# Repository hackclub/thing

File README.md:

<picture>
  <source media="(prefers-color-scheme: dark) and (max-width: 960px)" srcset="./thing.png">
  <source media="(prefers-color-scheme: dark) and (min-width: 961px)" width="50%" srcset="./thing.png">

  <source media="(prefers-color-scheme: light) and (max-width: 960px)" srcset="./thing-light.png">
  <source media="(prefers-color-scheme: light) and (min-width: 961px)" width="50%" srcset="./thing-light.png">

</picture>

Hey! Welcome to **The Thing**!

## Hey, what is this thing?
Have you seen those 80-part Swiss Army knives? I want us to make a PCB with that level of esotericism; a sprawling, over-the-top monstrosity.

Many Hack Clubbers will add a tool or something to the same PCB consecutively, and at the end I'll get \~10 made and send them off to some people you may or may not have seen on YouTube...
(and if you find me at a hackathon and you've added a subsystem to the board you may end up with one too (prob limited to 1 or 2)).

It'll end when 100 subsystems have been added or nobody adds a component for a week. Happy hacking!

## Current thing:

## How will it work?
* People will take turns adding their subsystem.
* Each person will get 2 days. If it's not merged after exactly 2 days, you'll be put at the back of the queue for another go and it'll be handed off to the next person. **I'll DM you a day or two before it's your turn to make sure you're ready. If you don't respond you might be skipped.**
* Merging requires me to be reasonably sure it'll work.

## What should my submission include?
* In the `/docs` directory, add a folder titled `IDX-USERNAME`, where `IDX` is your number in line, and `USERNAME` is your GitHub username.
  * For example, I'm the first person to go, so my folder is named `0-malted`.
  * In your folder, you'll need;
    * `doc.md`: Your writeup. Include detail about your subsystem! How you designed it, your calculations, tests, everything. Don't use an LLM, make it interesting, tell me a story!! :D
    * `pcb.png`: A screenshot of the PCB in Kicad's PCB editor, showing the entire PCB.
    * `pcb-3d.png`: Switch to View > 3D viewer and select "Render current view using raytracing". Again, we want to see the whole board!
    * `schematic.png`: A screenshot of the whole board's schematic.
    * `cad.png` **(OPTIONAL)**: If someone designs an enclosure or something (wink wink nudge nudge), show me a screenshot of it. You only need to do this if you've changed it.
    * `bom.csv`: Your bill of materials. Create and edit this manually. The price should be that of a single part (regardless of your `quantity`, **on the line item for 100 pieces**. It should be in USD without a dollar symbol.
      * For an exemplar BoM check mine out: `/docs/0-malted/bom.csv`. There's a template at `/docs/bom-template.csv`.
  * Make your schematic as complete as possible! When you double click your components you can add datasheets to help out others who might need to tie into your circuit or something in the future.

## Constraints
* Use Kicad `9.0.x`. Apparently, our project will be corrupted if we're on differing versions.
* Each BoM must not exceed $5 in parts. Assume 3D printing is free. If you have an especially cool idea I could be convinced to double it on a case-by-case basis :)
* Please strongly bias for parts in stock on Digikey.

## Tips
Finding parts can be tricky. Here's how I found the USB-C receptable I used in my circuit;
  1. Added a symbol to my schematic. I only wanted it for the 5V rail, so I found a symbol with the description "*USB Power-Only 6P Type-C Receptacle connector*". Seems okay.
  2. Opened the *footprint editor* and searched for "*usb c receptacle 6p*" (6P meaning it has 6 pins, which is minimal). I found a footprint named "*USB_C_Receptacle_GCT_USB4125-xx-x_6P_TopMnt_Horizontal*", which looked good. I liked the footprint because it had through-hole shield pins, meaning it would be less likely to be ripped off the board when pulling on it. The only other footprint which actually had 6 pins didn't have the through-hole shield.
  3. I searched on the internet for "*USB4125*". I found the [page from the manufacturer](https://gct.co/connector/usb4125) (GCT), which had links to Mouser and Digikey, amongst others. Heaven. It was slightly cheaper on Mouser so I went with that. It's comforting that it says *21230 In stock*.
  4. I double click on my component, click the library icon at the end of the "Footprint" table row, and searched for "*gct usb 4125*". Assigned it. Placed it on my PCB, and added it to my BoM! All done.

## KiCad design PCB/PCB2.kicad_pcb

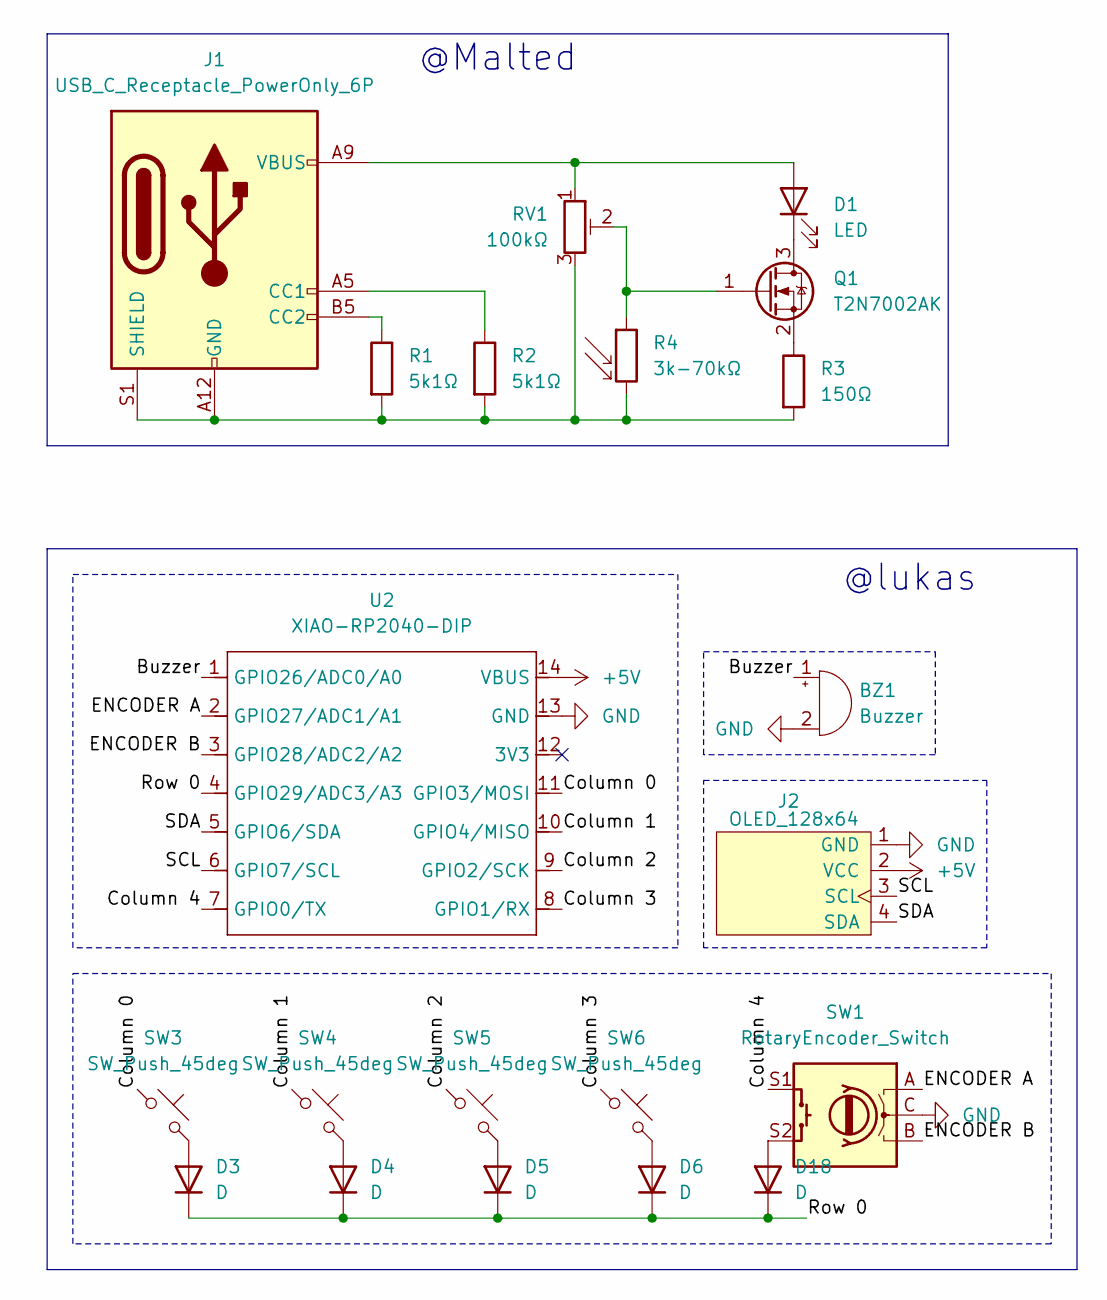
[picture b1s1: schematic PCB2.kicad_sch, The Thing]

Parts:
BZ1: Buzzer; Buzzer_12x9.5RM7.6
D1: LED; LED_D5.0mm_Clear
D3, D4, D5, D6, D18: D; Diode_SOD-123
J1: USB_C_Receptacle_PowerOnly_6P; USB_C_Receptacle_GCT_USB4125-xx-x-0190_6P_TopMnt_Horizontal
J2: OLED_128x64; OLED_128x32
Q1: T2N7002AK; SOT-23
R1, R2: 5k1Ω; R_0402_1005Metric
R3: 150Ω; R_0402_1005Metric
R4: 3k-70kΩ; R_LDR_5.1x4.3mm_P3.4mm_Vertical
RV1: 100kΩ; Potentiometer_Bourns_TC33X_Vertical
SW1: RotaryEncoder_Switch; RollerEncoder_Panasonic_EVQWGD001
SW3, SW4, SW5, SW6: SW_Push_45deg; MX-Solderable-1U
U2: XIAO-RP2040-DIP

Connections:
+5V: J2.2 (VCC), U2.14 (VBUS)
/BUZZER PASSIVE: BZ1.1 (+), U2.1 (GPIO26/ADC0/A0)
/Column 0: SW3.1, U2.11 (GPIO3/MOSI)
/Column 1: SW4.1, U2.10 (GPIO4/MISO)
/Column 2: SW5.1, U2.9 (GPIO2/SCK)
/Column 3: SW6.1, U2.8 (GPIO1/RX)
/Column 4: SW1.S1, U2.7 (GPIO0/TX)
/ENCODER A: SW1.A, U2.2 (GPIO27/ADC1/A1)
/ENCODER B: SW1.B, U2.3 (GPIO28/ADC2/A2)
/Row 0: D3.1 (K), D4.1 (K), D5.1 (K), D6.1 (K), D18.1 (K), U2.4 (GPIO29/ADC3/A3)
/SCL: J2.3 (SCL), U2.6 (GPIO7/SCL)
/SDA: J2.4 (SDA), U2.5 (GPIO6/SDA)
GND: BZ1.2 (-), J2.1 (GND), SW1.C, U2.13 (GND)
unnamed: D1.2 (A), J1.A9 (VBUS), J1.B9 (VBUS), RV1.1
unnamed: D1.1 (K), Q1.3 (D)
unnamed: D3.2 (A), SW3.2
unnamed: D4.2 (A), SW4.2
unnamed: D5.2 (A), SW5.2
unnamed: D6.2 (A), SW6.2
unnamed: D18.2 (A), SW1.S2
unnamed: J1.A5 (CC1), R2.1
unnamed: J1.B5 (CC2), R1.1
unnamed: J1.A12 (GND), J1.B12 (GND), J1.S1 (SHIELD), R1.2, R2.2, R3.2, R4.2, RV1.3
unnamed: Q1.1 (G), R4.1, RV1.2
unnamed: Q1.2 (S), R3.1

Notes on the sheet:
@Malted
@lukas

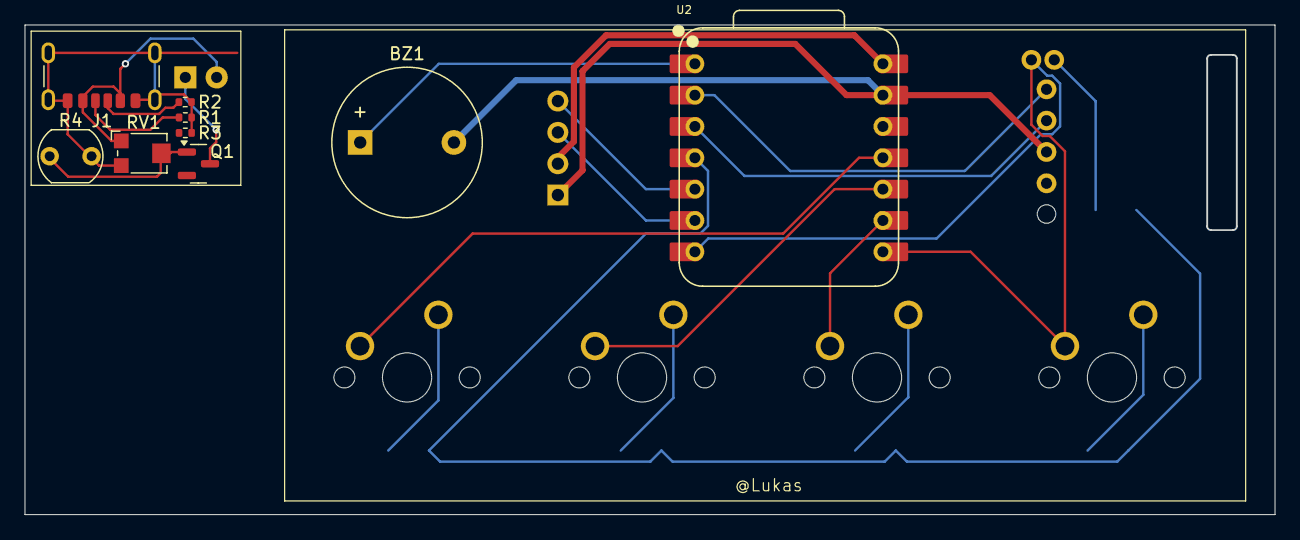
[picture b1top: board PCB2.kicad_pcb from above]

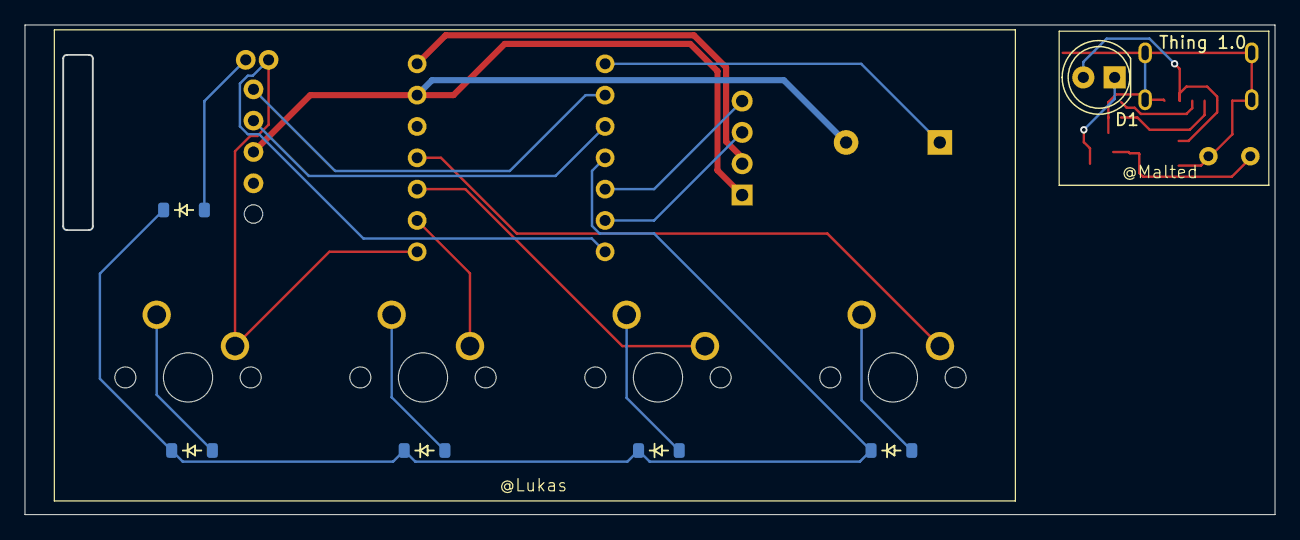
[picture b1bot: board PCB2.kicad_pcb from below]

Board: 2 copper layers, 101.2 x 39.6 mm, 21 parts (6 on the bottom side), 25 nets.

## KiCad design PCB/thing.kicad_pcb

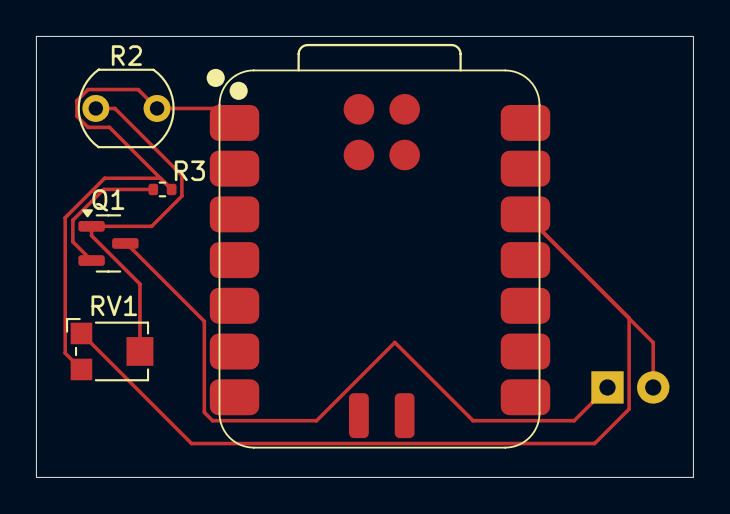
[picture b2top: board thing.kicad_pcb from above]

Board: 2 copper layers, 36.5 x 24.5 mm, 6 parts (1 on the bottom side), 5 nets.

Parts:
D1: LED; LED_D5.0mm_Clear
Q1: SOT-23
R2: 3k-70kΩ; R_LDR_5.1x4.3mm_P3.4mm_Vertical
R3: 68Ω; R_0402_1005Metric
RV1: 100kΩ; Potentiometer_Bourns_TC33X_Vertical
U1: Seeed Studio XIAO SAMD21; XIAO-RP2040-SMD

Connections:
unnamed: D1.2 (A), RV1.1, U1.12 (3V3)
unnamed: D1.1 (K), Q1.3 (D)
unnamed: Q1.1 (G), R2.1, RV1.2
unnamed: Q1.2 (S), R3.1
unnamed: R2.2, R3.2, RV1.3, U1.1 (PA02_A0_D0)

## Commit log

2025-04-04 Create site
2025-04-05 Create PCB
2025-04-05 Route PCB
2025-04-05 Create hero element
2025-04-05 It's responsive
2025-04-05 Fix positioning
2025-04-05 Add registration fillout
2025-04-05 Fix underline positioning
2025-04-06 Add background and fix SVG
2025-04-06 Add writeups
2025-04-06 Rename writeups and add screenshots
2025-04-06 Clean up board
2025-04-06 Change thing readme
2025-04-06 Bobdl
2025-04-10 Add queue
2025-04-11 Reroute PCB
2025-04-11 Finish documentation
2025-04-11 Add bill of materials template
2025-04-11 Amend instructions
2025-04-11 Filter emails out and make sure the slack ID is valid
2025-04-11 Add 5k1 CC resistors to negotiate 5V
2025-04-11 Add DRC hepler image
2025-04-11 Document CC resistors
2025-04-11 Add and route CC 5k1Ω resistors
2025-04-12 Change z index
2025-04-14 Tie all xiao gnd outs to ground
2025-04-14 Revert "Change z index"
    This reverts commit 9002087e978e21d72fad64b1fa667c59dc428344.
2025-04-14 Clean up schematic
2025-04-14 Revert to malted's PCB
2025-04-18 Rebuilt PCB
2025-04-18 Move LED to back of PCB
2025-04-18 Add instructions in PCB file
2025-04-18 Add the current thing to the readme
2025-04-19 Add a title to the site
2025-05-06 add my project files
